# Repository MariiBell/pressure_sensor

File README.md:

# pressure_sensor 
---
в master ветке разделила на две платки: logic_pcb - логика, sensor_pcb - где будут приклеены тензорезисторы, logic_sensor_pcb - старый проект до разделения на две платы <br>
Сделала крепежные отверстия <br>
И общую 3д модель

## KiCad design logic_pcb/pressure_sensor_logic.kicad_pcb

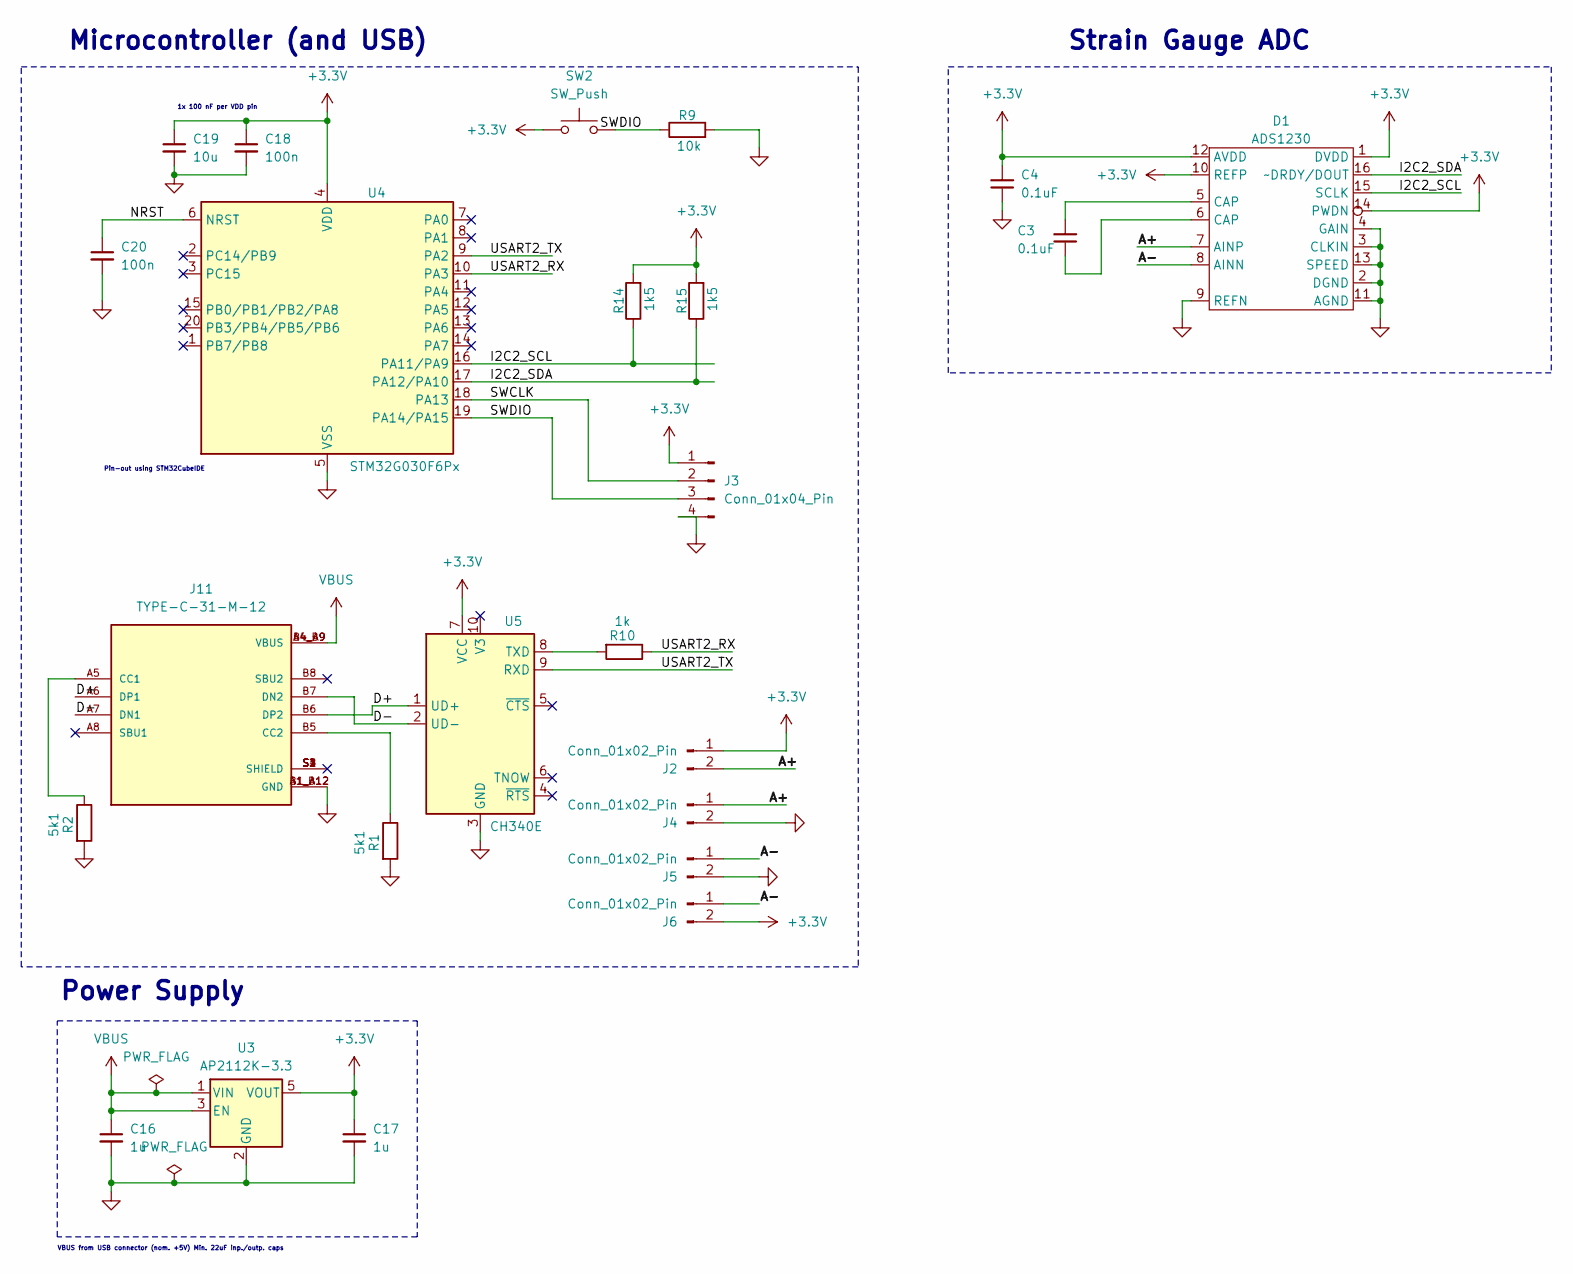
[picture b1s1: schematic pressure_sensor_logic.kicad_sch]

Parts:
C3, C4: 0.1uF; C_0603_1608Metric
C16, C17: 1u; C_0805_2012Metric
C18, C20: 100n; C_0603_1608Metric
C19: 10u; C_0603_1608Metric
D1: ADS1230; SSOP-16_4.4x5.2mm_P0.65mm
J2, J4, J5, J6: Conn_01x02_Pin; PinHeader_1x02_P1.00mm_Vertical
J3: Conn_01x04_Pin; PinHeader_1x04_P1.00mm_Vertical
J11: TYPE-C-31-M-12; HRO_TYPE-C-31-M-12; PARTREV 2020.12.08
R1, R2: 5k1; R_0603_1608Metric
R9: 10k; R_0603_1608Metric
R10: 1k; R_0603_1608Metric
R14, R15: 1k5; R_0603_1608Metric
SW2: SW_Push; SW_SPST_B3U-1000P-B
U3: AP2112K-3.3; SOT-23-5
U4: STM32G030F6Px; TSSOP-20_4.4x6.5mm_P0.65mm
U5: CH340E; MSOP-10_3x3mm_P0.5mm

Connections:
+3.3V: C4.2, C17.1, C18.1, C19.1, D1.1 (DVDD), D1.10 (REFP), D1.12 (AVDD), D1.14 (PWDN), J2.1, J3.1, J6.2, R14.2, R15.2, SW2.2, U3.5 (VOUT), U4.4 (VDD), U5.7 (VCC)
/A+: D1.7 (AINP), J2.2, J4.1
/A-: D1.8 (AINN), J5.1, J6.1
/D+: J11.A6 (DP1), J11.B6 (DP2), U5.1 (UD+)
/D-: J11.A7 (DN1), J11.B7 (DN2), U5.2 (UD-)
/I2C2_SCL: D1.15 (SCLK), R14.1, U4.16 (PA11/PA9)
/I2C2_SDA: D1.16 (~DRDY/DOUT), R15.1, U4.17 (PA12/PA10)
/NRST: C20.1, U4.6 (NRST)
/SWCLK: J3.2, U4.18 (PA13)
/SWDIO: J3.3, R9.1, SW2.1, U4.19 (PA14/PA15)
/USART2_RX: R10.1, U4.10 (PA3)
/USART2_TX: U4.9 (PA2), U5.9 (RXD)
GND: C4.1, C16.2, C17.2, C18.2, C19.2, C20.2, D1.2 (DGND), D1.3 (CLKIN), D1.4 (GAIN), D1.9 (REFN), D1.11 (AGND), D1.13 (SPEED), J3.4, J4.2, J5.2, J11.A1_B12 (GND), J11.B1_A12 (GND), R1.2, R2.2, R9.2, U3.2 (GND), U4.5 (VSS), U5.3 (GND)
unnamed: C3.1, D1.6 (CAP)
unnamed: C3.2, D1.5 (CAP)
unnamed: J11.A5 (CC1), R2.1
unnamed: J11.B5 (CC2), R1.1
unnamed: R10.2, U5.8 (TXD)
VBUS: C16.1, J11.A4_B9 (VBUS), J11.B4_A9 (VBUS), U3.1 (VIN), U3.3 (EN)

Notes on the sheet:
1x 100 nF per VDD pin
Microcontroller (and USB)
Strain Gauge ADC
VBUS from USB connector (nom. +5V) Min. 22uF inp./outp. caps
Power Supply
Pin-out using STM32CubeIDE

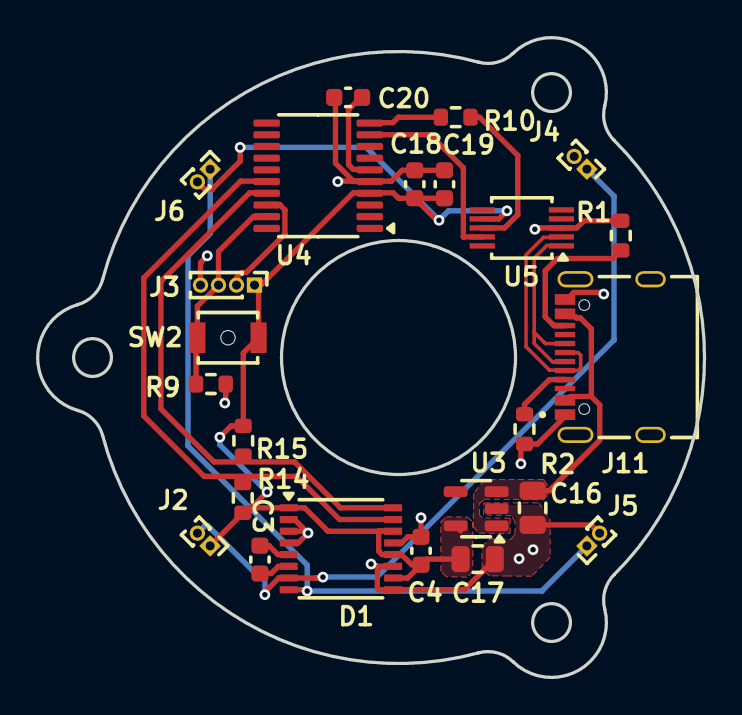
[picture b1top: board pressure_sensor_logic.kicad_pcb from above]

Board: 2 copper layers, 37.1 x 35.5 mm, 24 parts (0 on the bottom side), 19 nets.

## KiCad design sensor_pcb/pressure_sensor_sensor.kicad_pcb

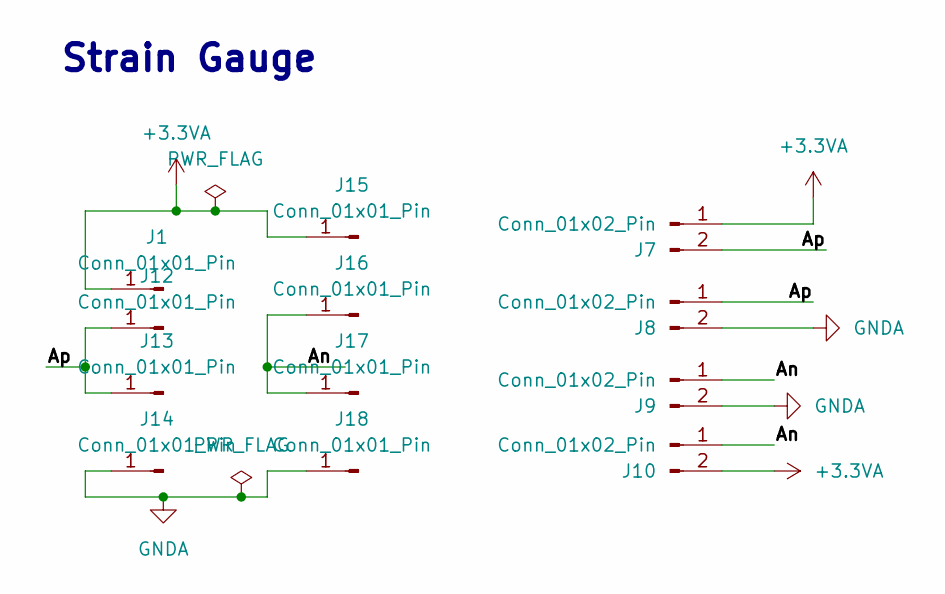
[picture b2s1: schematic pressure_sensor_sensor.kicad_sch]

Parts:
J1, J12, J13, J14, J15, J16, J17, J18: Conn_01x01_Pin; PinHeader_1x01_P1.00mm_Vertical
J7, J8, J9, J10: Conn_01x02_Pin; PinHeader_1x02_P1.00mm_Vertical

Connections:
+3.3VA: J1.1, J7.1, J10.2, J15.1
/An: J9.1, J10.1, J16.1, J17.1
/Ap: J7.2, J8.1, J12.1, J13.1
GNDA: J8.2, J9.2, J14.1, J18.1

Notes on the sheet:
Strain Gauge

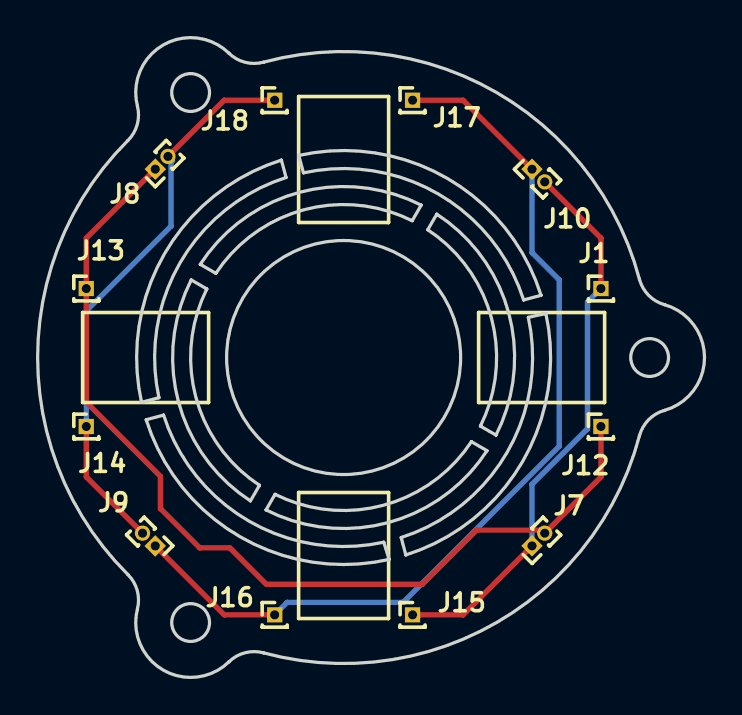
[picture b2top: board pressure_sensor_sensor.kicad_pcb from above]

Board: 2 copper layers, 37.1 x 35.5 mm, 12 parts (0 on the bottom side), 4 nets.

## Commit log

2024-05-16 Add kikad folder
2024-05-16 separation_of_logic_and_sensor_boards
2024-05-16 mounting_holes_added
2024-05-16 alignement_corrected
2024-05-16 3d_start_point_added
2024-05-17 gerbers_generated
2024-05-17 Create README.md# pressure_sensor --- в master ветке разделила на две платки: logic_pcb - логика, sensor_pcb - где будут приклеены тензорезисторы, logic_sensor_pcb - старый проект до разделения на дв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
2024-05-17 3d_model_modified
